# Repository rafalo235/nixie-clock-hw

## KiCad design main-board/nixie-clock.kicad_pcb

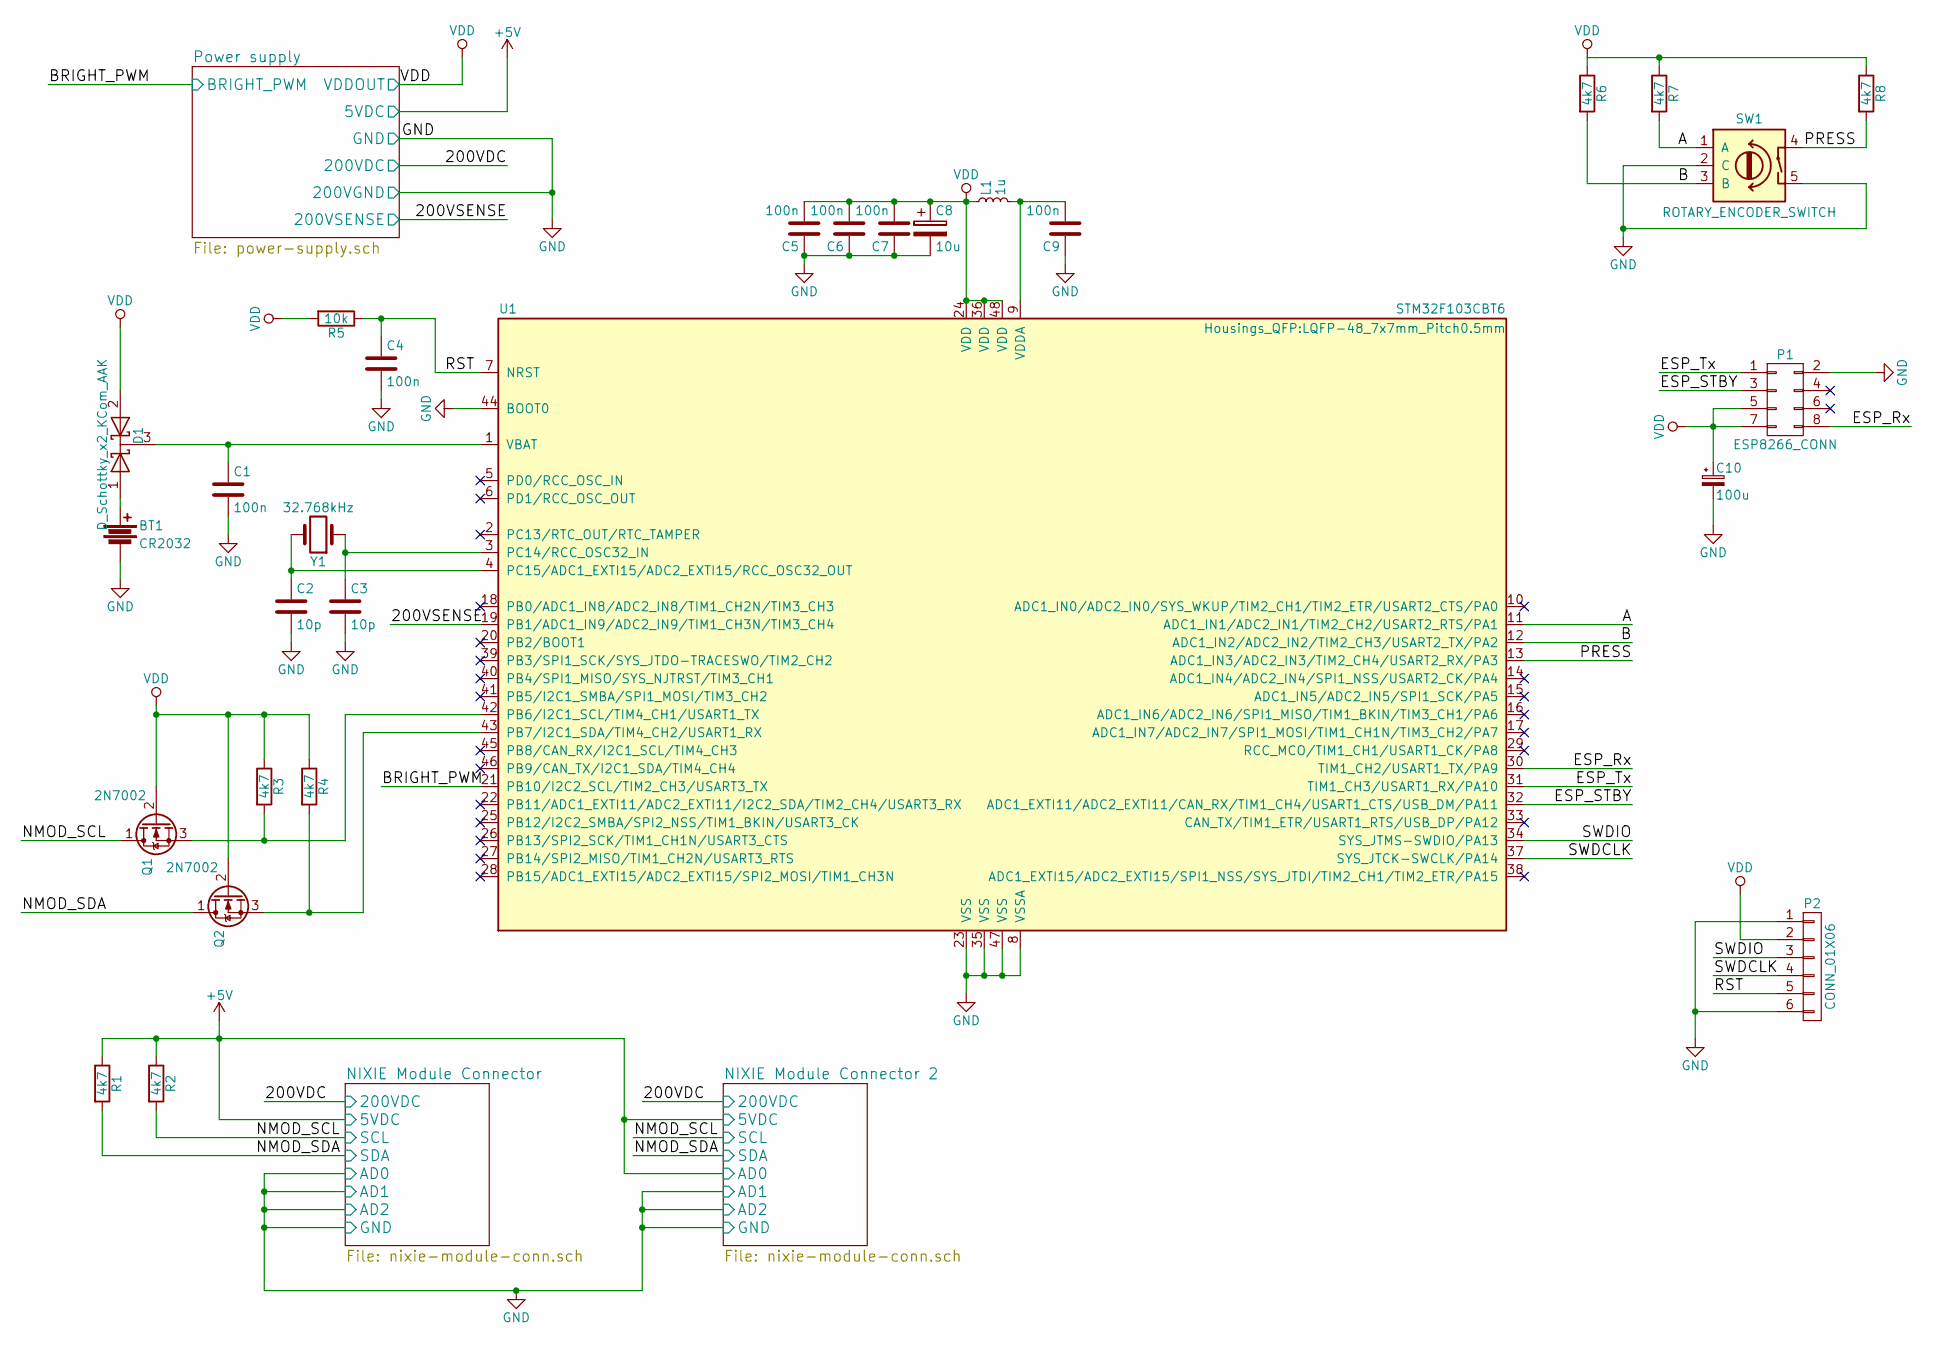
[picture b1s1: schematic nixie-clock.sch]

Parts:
BT1: CR2032; CR2032H
C1, C4, C5, C6, C7, C9: 100n; C_0805_HandSoldering
C2, C3: 10p; C_0805_HandSoldering
C8: 10u; TantalC_SizeB_EIA-3528_HandSoldering
C10: 100u; TantalC_SizeC_EIA-6032_HandSoldering
D1: D_Schottky_x2_KCom_AAK; SOT-23_Handsoldering
L1: 1u; Choke_SMD_1206_Handsoldering
P1: ESP8266_CONN; Pin_Header_Straight_SMT_02x04
P2: CONN_01X06; Pin_Header_Straight_SMT_02x03
Q1, Q2: 2N7002; SOT-23_Handsoldering
R1, R2, R3, R4, R6, R7, R8: 4k7; R_0805_HandSoldering
R5: 10k; R_0805_HandSoldering
SW1: ROTARY_ENCODER_SWITCH; Pin_Header_Straight_SMT_02x03
U1: STM32F103CBT6; LQFP-48_7x7mm_Pitch0.5mm
Y1: 32.768kHz; Crystal_Round_Vertical_3mm_BigPad; Part no. LFXTAL002996BULK

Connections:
+5V: R1.1, R2.1; also elsewhere on the board
/200VSENSE: U1.19 (PB1/ADC1_IN9/ADC2_IN9/TIM1_CH3N/TIM3_CH4); also elsewhere on the board
/A: R7.2, SW1.1 (A), U1.11 (ADC1_IN1/ADC2_IN1/TIM2_CH2/USART2_RTS/P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)
/B: R6.2, SW1.3 (B), U1.12 (ADC1_IN2/ADC2_IN2/TIM2_CH3/USART2_TX/PA2)
/BRIGHT_PWM: U1.21 (PB10/I2C2_SCL/TIM2_CH3/USART3_TX); also elsewhere on the board
/ESP_Rx: P1.8, U1.30 (TIM1_CH2/USART1_TX/PA9)
/ESP_STBY: P1.3, U1.32 (ADC1_EXTI11/ADC2_EXTI11/CAN_RX/TIM1_CH4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)
/ESP_Tx: P1.1, U1.31 (TIM1_CH3/USART1_RX/PA10)
/NMOD_SCL: Q1.1 (D), R2.2; also elsewhere on the board
/NMOD_SDA: Q2.1 (D), R1.2; also elsewhere on the board
/PRESS: R8.2, SW1.4, U1.13 (ADC1_IN3/ADC2_IN3/TIM2_CH4/USART2_RX/PA3)
/RST: C4.1, P2.5, R5.1, U1.7 (NRST)
/SWDCLK: P2.4, U1.37 (SYS_JTCK-SWCLK/PA14)
/SWDIO: P2.3, U1.34 (SYS_JTMS-SWDIO/PA13)
GND: BT1.2, C1.2, C2.2, C3.2, C4.2, C5.1, C6.1, C7.1, C8.2, C9.1, C10.2, P1.2, P2.1, P2.6, SW1.2 (C), SW1.5, U1.8 (VSSA), U1.23 (VSS), U1.35 (VSS), U1.44 (BOOT0), U1.47 (VSS); also elsewhere on the board
unnamed: BT1.1, D1.1 (A)
unnamed: C1.1, D1.3 (K), U1.1 (VBAT)
unnamed: C2.1, U1.4 (PC15/ADC1_EXTI15/ADC2_EXTI15/RCC_OSC32_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), Y1.2
unnamed: C3.1, U1.3 (PC14/RCC_OSC32_IN), Y1.1
unnamed: C9.2, L1.2, U1.9 (VDDA)
unnamed: Q1.3 (S), R3.2, U1.42 (PB6/I2C1_SCL/TIM4_CH1/USART1_TX)
unnamed: Q2.3 (S), R4.2, U1.43 (PB7/I2C1_SDA/TIM4_CH2/USART1_RX)
VDD: C5.2, C6.2, C7.2, C8.1, C10.1, D1.2 (A), L1.1, P1.5, P1.7, P2.2, Q1.2 (G), Q2.2 (G), R3.1, R4.1, R5.2, R6.1, R7.1, R8.1, U1.24 (VDD), U1.36 (VDD), U1.48 (VDD); also elsewhere on the board

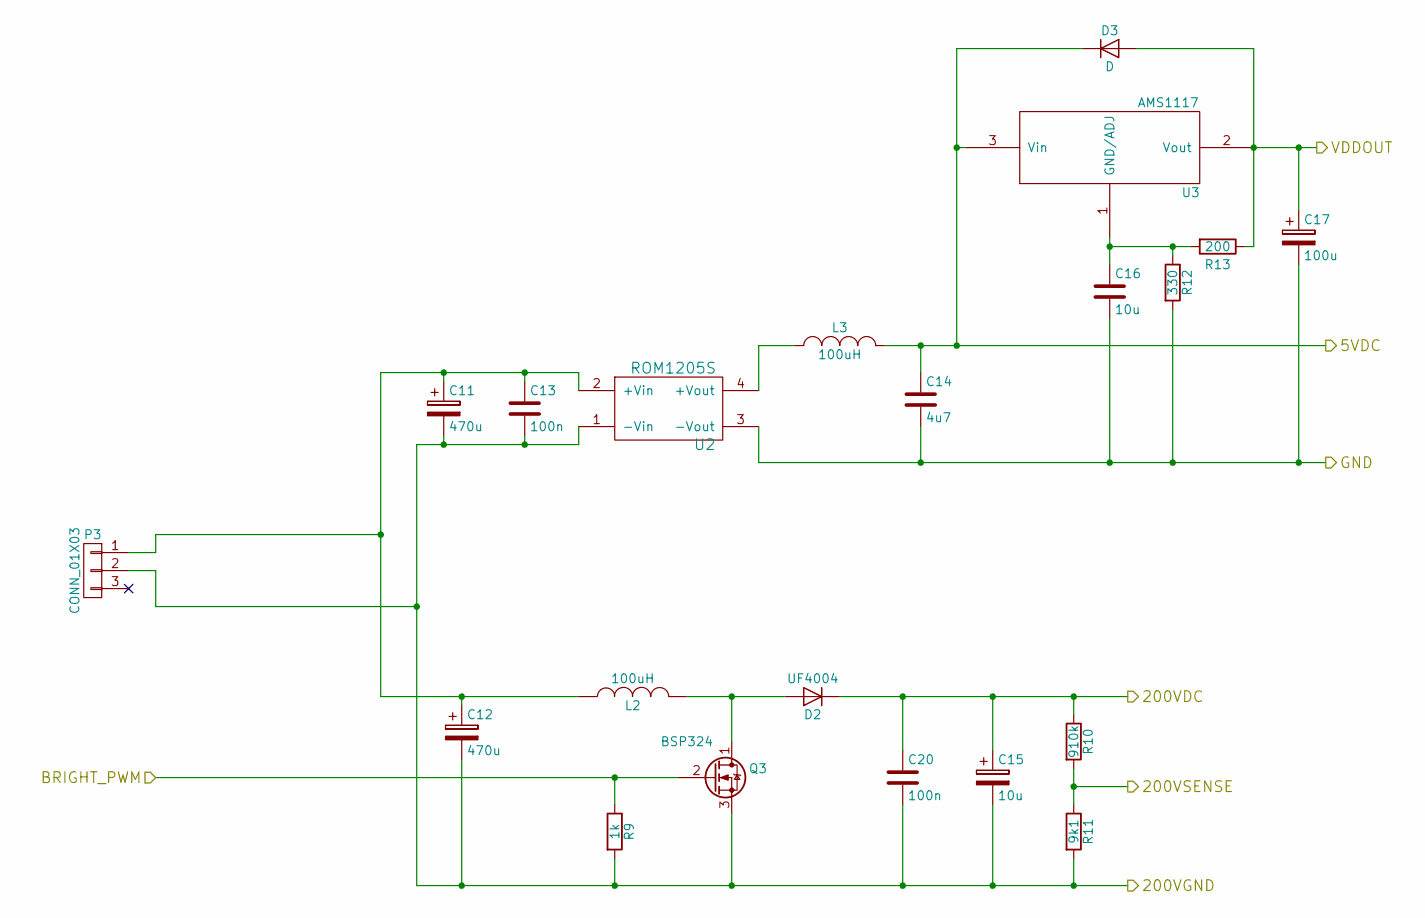
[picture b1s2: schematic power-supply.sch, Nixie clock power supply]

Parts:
C11, C12: 470u; c_elec_10x10
C13: 100n; C_0805_HandSoldering
C14: 4u7; C_0805_HandSoldering
C15: 10u; C_Radial_D10_L20_P5; Part no. TVX2F100MCD
C16: 10u; TantalC_SizeB_EIA-3528_HandSoldering
C17: 100u; TantalC_SizeC_EIA-6032_HandSoldering
C20: 100n; C_1812_HandSoldering
D2: UF4004; Diode_DO-41_SOD81_Vertical_AnodeUp
D3: D; MiniMELF_Handsoldering
L2: 100uH; Neosid_Inductor_Sd8; Part no. 5900-103-RC
L3: 100uH; R_1812_HandSoldering
P3: CONN_01X03; BARREL_JACK
Q3: BSP324; SOT-223; Part no. BSP324H6327XTSA1
R9: 1k; R_0805_HandSoldering
R10: 910k; R_1206_HandSoldering
R11: 9k1; R_1206_HandSoldering
R12: 330; R_0805_HandSoldering
R13: 200; R_0805_HandSoldering
U2: ROM1205S; SIP4
U3: AMS1117; TO-252-2Lead

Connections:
+5V: C14.1, D3.1 (K), L3.2, U3.3 (Vin); also elsewhere on the board
/200VDC: C15.1, C20.1, D2.1 (K), R10.1; also elsewhere on the board
/200VSENSE: R10.2, R11.1; also elsewhere on the board
/BRIGHT_PWM: Q3.2 (G), R9.1; also elsewhere on the board
GND: C11.2, C12.2, C13.2, C14.2, C15.2, C16.2, C17.2, C20.2, P3.2, Q3.3 (S), R9.2, R11.2, R12.2, U2.1 (-Vin), U2.3 (-Vout); also elsewhere on the board
unnamed: C11.1, C12.1, C13.1, L2.1, P3.1, U2.2 (+Vin)
unnamed: C16.1, R12.1, R13.2, U3.1 (GND/ADJ)
unnamed: D2.2 (A), L2.2, Q3.1 (D)
unnamed: L3.1, U2.4 (+Vout)
VDD: C17.1, D3.2 (A), R13.1, U3.2 (Vout); also elsewhere on the board

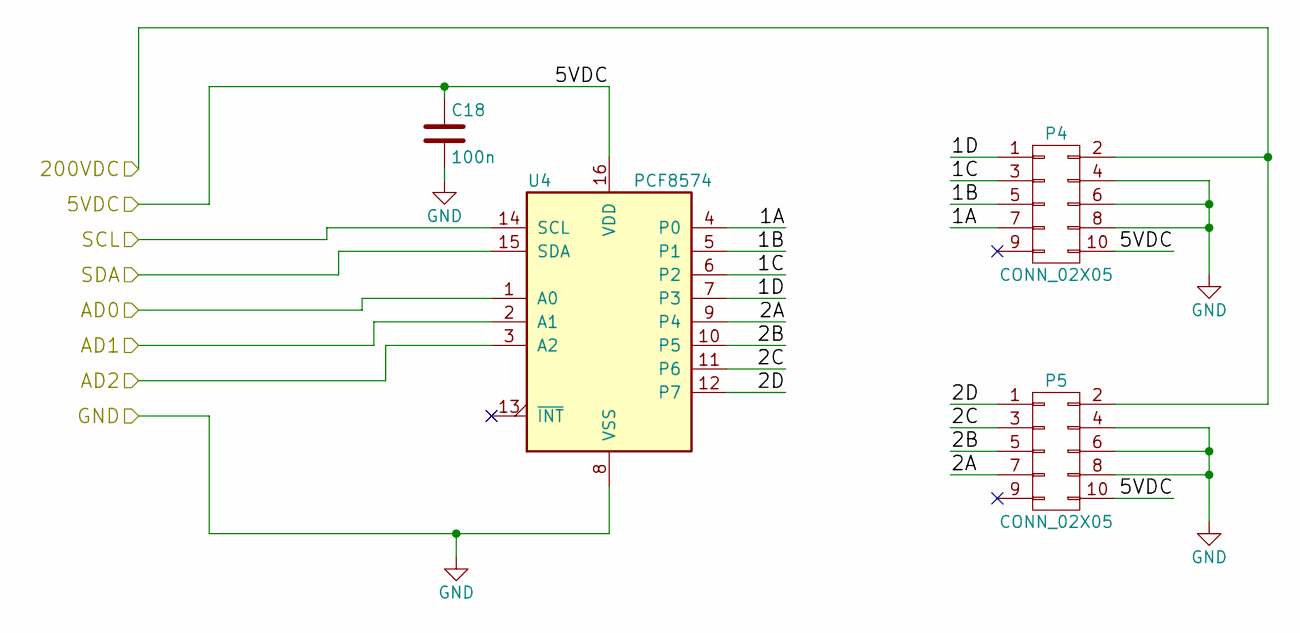
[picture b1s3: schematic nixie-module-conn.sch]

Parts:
C18: 100n; C_0805_HandSoldering
P4, P5: CONN_02X05; Pin_Header_Straight_SMT_02x05
U4: PCF8574; SOIC-16W_7.5x10.3mm_Pitch1.27mm

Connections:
+5V: C18.1, P4.10, P5.10, U4.16 (VDD); also elsewhere on the board
/200VDC: P4.2, P5.2; also elsewhere on the board
/NIXIE Module Connector/1A: P4.7, U4.4 (P0)
/NIXIE Module Connector/1B: P4.5, U4.5 (P1)
/NIXIE Module Connector/1C: P4.3, U4.6 (P2)
/NIXIE Module Connector/1D: P4.1, U4.7 (P3)
/NIXIE Module Connector/2A: P5.7, U4.9 (P4)
/NIXIE Module Connector/2B: P5.5, U4.10 (P5)
/NIXIE Module Connector/2C: P5.3, U4.11 (P6)
/NIXIE Module Connector/2D: P5.1, U4.12 (P7)
/NMOD_SCL: U4.14 (SCL); also elsewhere on the board
/NMOD_SDA: U4.15 (SDA); also elsewhere on the board
GND: C18.2, P4.4, P4.6, P4.8, P5.4, P5.6, P5.8, U4.1 (A0), U4.2 (A1), U4.3 (A2), U4.8 (VSS); also elsewhere on the board

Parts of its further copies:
C19: 100n; C_0805_HandSoldering
P6, P7: CONN_02X05; Pin_Header_Straight_SMT_02x05
U5: PCF8574; SOIC-16W_7.5x10.3mm_Pitch1.27mm

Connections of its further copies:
+5V: C19.1, P6.10, P7.10, U5.1 (A0), U5.16 (VDD); also elsewhere on the board
/200VDC: P6.2, P7.2; also elsewhere on the board
/NIXIE Module Connector 2/1A: P6.7, U5.4 (P0)
/NIXIE Module Connector 2/1B: P6.5, U5.5 (P1)
/NIXIE Module Connector 2/1C: P6.3, U5.6 (P2)
/NIXIE Module Connector 2/1D: P6.1, U5.7 (P3)
/NIXIE Module Connector 2/2A: P7.7, U5.9 (P4)
/NIXIE Module Connector 2/2B: P7.5, U5.10 (P5)
/NIXIE Module Connector 2/2C: P7.3, U5.11 (P6)
/NIXIE Module Connector 2/2D: P7.1, U5.12 (P7)
/NMOD_SCL: U5.14 (SCL); also elsewhere on the board
/NMOD_SDA: U5.15 (SDA); also elsewhere on the board
GND: C19.2, P6.4, P6.6, P6.8, P7.4, P7.6, P7.8, U5.2 (A1), U5.3 (A2), U5.8 (VSS); also elsewhere on the board

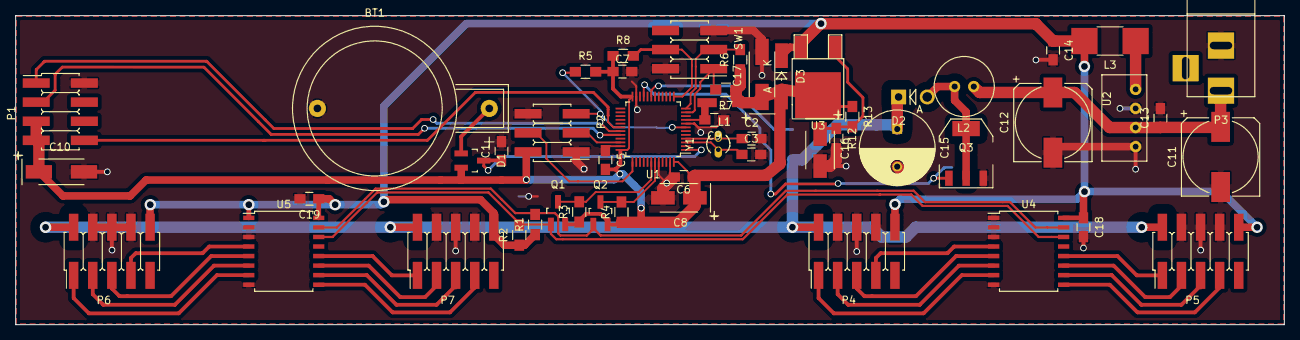
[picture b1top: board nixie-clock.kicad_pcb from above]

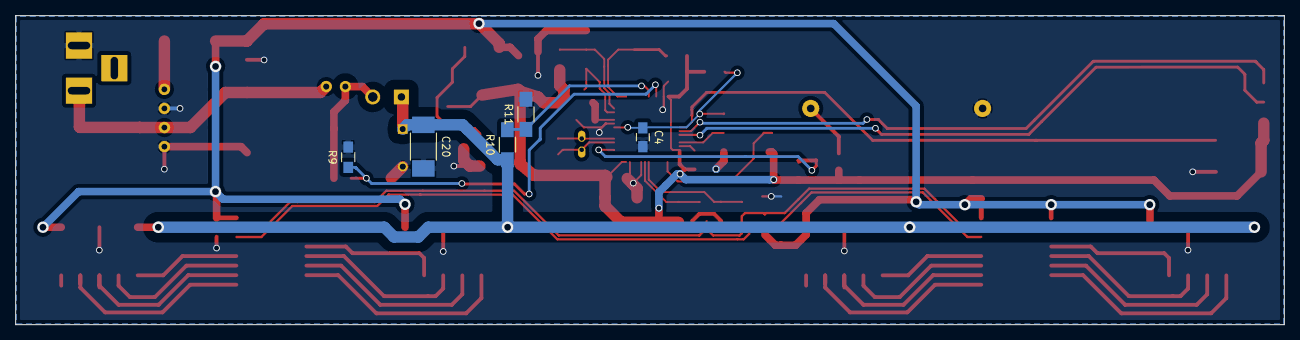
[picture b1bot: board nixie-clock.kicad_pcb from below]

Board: 2 copper layers, 168.7 x 41.1 mm, 57 parts (5 on the bottom side), 44 nets.

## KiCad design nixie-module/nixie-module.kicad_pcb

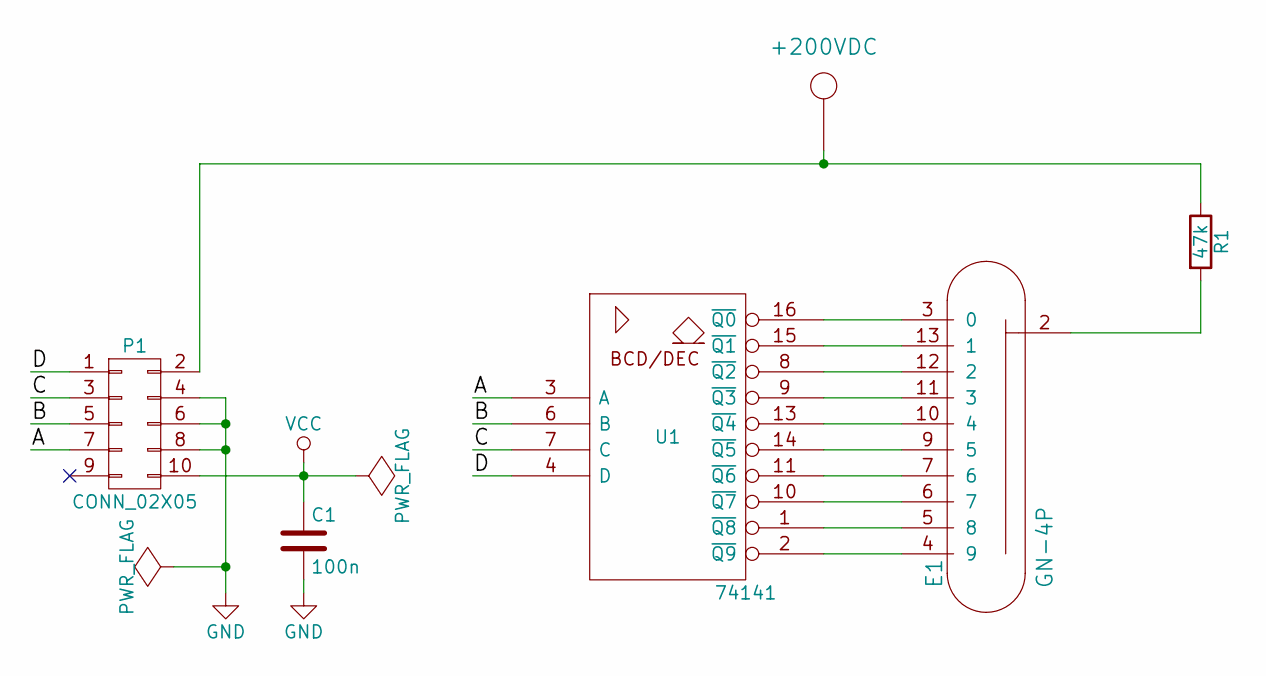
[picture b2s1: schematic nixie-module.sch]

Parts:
C1: 100n; C_0805_HandSoldering
E1: GN-4P; gn-4p-gniazdo
P1: CONN_02X05; Pin_Header_Angled_2x05
R1: 47k; R_1812_HandSoldering
U1: 74141; DIP-16_W7.62mm_LongPads

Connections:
/A: P1.7, U1.3 (A)
/B: P1.5, U1.6 (B)
/C: P1.3, U1.7 (C)
/D: P1.1, U1.4 (D)
GND: C1.2, P1.4, P1.6, P1.8, U1.12 (GND)
unnamed: E1.2, R1.2
unnamed: E1.3 (0), U1.16 (~Q0)
unnamed: E1.4 (9), U1.2 (~Q9)
unnamed: E1.5 (8), U1.1 (~Q8)
unnamed: E1.6 (7), U1.10 (~Q7)
unnamed: E1.7 (6), U1.11 (~Q6)
unnamed: E1.9 (5), U1.14 (~Q5)
unnamed: E1.10 (4), U1.13 (~Q4)
unnamed: E1.11 (3), U1.9 (~Q3)
unnamed: E1.12 (2), U1.8 (~Q2)
unnamed: E1.13 (1), U1.15 (~Q1)
unnamed: P1.2, R1.1
VCC: C1.1, P1.10, U1.5 (VCC)

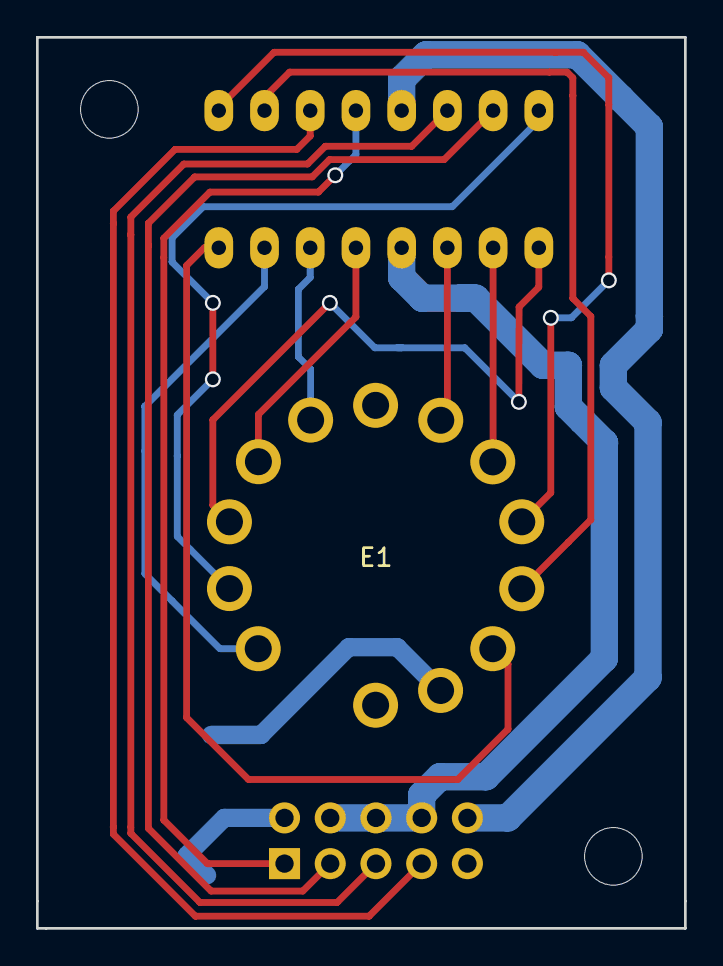
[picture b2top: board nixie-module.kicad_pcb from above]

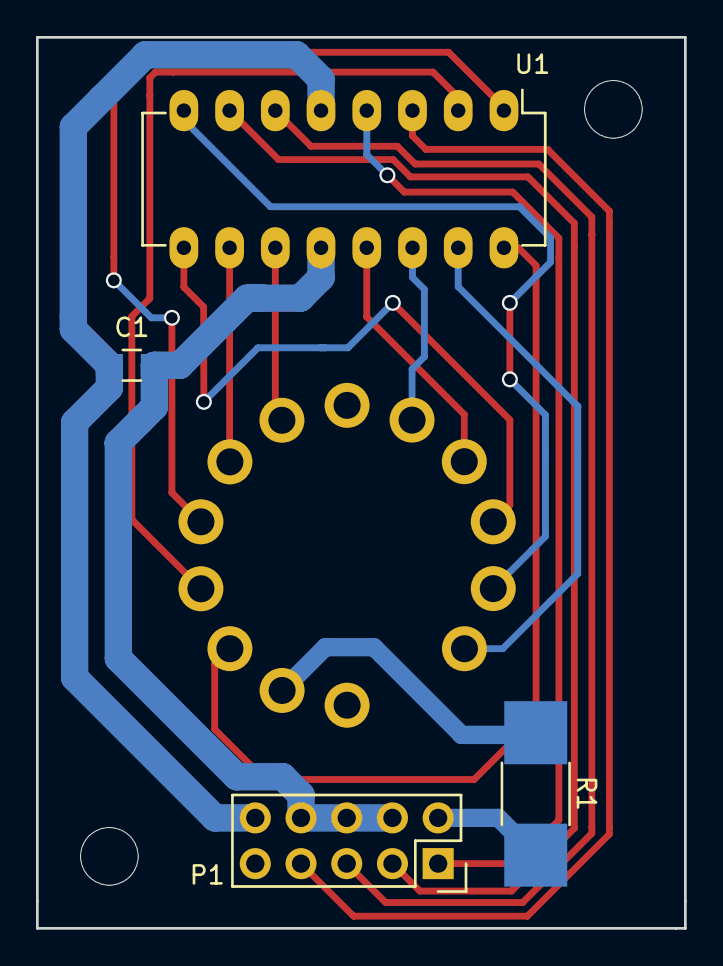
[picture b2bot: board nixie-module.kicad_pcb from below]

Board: 2 copper layers, 36.0 x 49.5 mm, 5 parts (3 on the bottom side), 18 nets.

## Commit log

2016-10-21 Pliki projektu
2016-10-21 Wybor procesora
2016-10-21 Dodanie oscylatorow 8MHz i 32kHz
2016-10-21 Usuniecie oscylatora 8MHz; zasilanie bateryjne
2016-10-29 Zasilanie ukladu - rozpoczete
2016-10-31 Wyprowadzenie VDD (3,3V); komentarze
2016-10-31 Wyprowadzenia do modulu ESP8266
2016-10-31 Kontrola jasnosci NIXIE
2016-11-01 Dokumentacja BCD-to-Decimal SN74141N
2016-11-01 Rozdzielenie projektu
2016-11-01 Modul lampy NIXIE
2016-11-01 GPIO Expander - podlaczenie do STM32; wyprowadzenia dla modulow NIXIE; zasilanie - do poprawki (GPIO Expander zasilany z 5V - STM 3,3V
2016-11-01 Dokumentacja PCF8574
2016-11-07 Dokumentacja STM32F103CBT6; poprawki zasilania, podciagniecie linii SDA i SCL, kondensator przy ESP8266 #1
2016-11-08 Poprawka zasilania stm32 i esp; VSS-GND
2016-11-11 #1 - enkoder zamiast potencjometru; pomiar napiecia zarzenia; SWD; BOOT0 do masy
2016-11-11 #1 - zmiana wartosci kondensator do typuszeregu, usuniecie D2, UF4004 na D4, przyciagniecie do masy bramki Q1, bezpiecznik na wejsciu przetwornicy, gniazdo IEC C7, 100n na zasilaniu PCF8574
2016-11-11 #1 - Przetwornica DC/DC 12V/5V
2016-11-11 #1 - dokumentacja ROM-1205S; usuniecie komentarza
2016-11-12 #1 - stabilizator LDO AMS1117-3.3V
2016-11-12 Niezapisane zmiany
2016-11-12 Polaczenie masy wyjscia ROM-1205S z masa 200V (-Vin z -Vout)
2016-11-18 #1 - Poprawienie otoczenia ukladow od zasilania; tolerancja 1% rezystorow dzielnika pomiarowego; usuniecie kondensatora filtrujacego wyjscie z enkodera; oddalenie od siebie linii (przeniesienie 200VS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
2016-11-21 Kondensator przy zasilaniu ukladu 74141
2016-11-21 Zewnetrzny zasilacz 12V
2016-11-25 Oznaczenie MOSFET-ow od I2C; pojemnosc do filtrowania wysokich czestotliwosci za przetwornica boost; obudowy wiekszosci elementow
2016-11-25 Dobranie parametrow przetwornicy boost + obudowy; obudowa do dlawika z ROM1205S
2016-11-26 Obudowa SIP4 do ukladu ROM1205S; utworzenie lokalnej biblioteki footprintow
2016-11-28 Rozpoczecie projektu PCB
2016-11-30 Poprawione polaczenie sciezek; zmiana nazwy wyjscia VDD
2016-12-01 usunięcie błędnego połączenia VDD z +5V
2016-12-01 Temp
2016-12-14 Obrys plytki 40% elementow
2016-12-15 Do zrobienia przelotki; elementy rozmieszczone
2016-12-15 Do sprawdzenia
2016-12-15 Poprawka - dioda pod napieciem z wiekszym odstepem
2016-12-15 Przypisanie elementow (poza lampa) do obudow
2016-12-15 Poprawienie pinow w gniezdzie
2016-12-15 Lokalna biblioteka footprint - nixie module; tymczasowe gniazdo do lampy
2016-12-16 Gotowe gniazdo na GN4P - wlutowanie nitow 1mm
2016-12-16 Do sprawdzenia modul NIXIE
2016-12-16 Reguly DRC; wymiary plytki
2016-12-16 Odwrocenie numeracji pinow w zlaczu od modulu NIXIE
2016-12-16 Poprawienie rozmiarow modulu NIXIE - lampa kolidowalaby z lutami od 74141 i listwy
2016-12-20 Modyfikacja sciezek modulu NIXIE
2016-12-20 Przesuniecie etykiet na module NIXIE
2016-12-20 Poprawki; otwory montazowe; obrys
2016-12-20 Generowanie gerberow
2016-12-20 Poprawiona plytka
2016-12-22 poprawki prowadzenia ścieżek, footprintów, zmniejszenie rozmiaru płytki pod lampę nixie
2016-12-22 poprawka oznaczenia lampy na płytce, wygenerowanie plików produkcyjnych do nixie-module
2016-12-22 wygenerowanie plików produkcyjnych do płytki main-board
2017-04-15 Dokumentacja z NXP - wlutowany uklad (PCF8574AT) ma inny adres niz Microchip PCF8574
